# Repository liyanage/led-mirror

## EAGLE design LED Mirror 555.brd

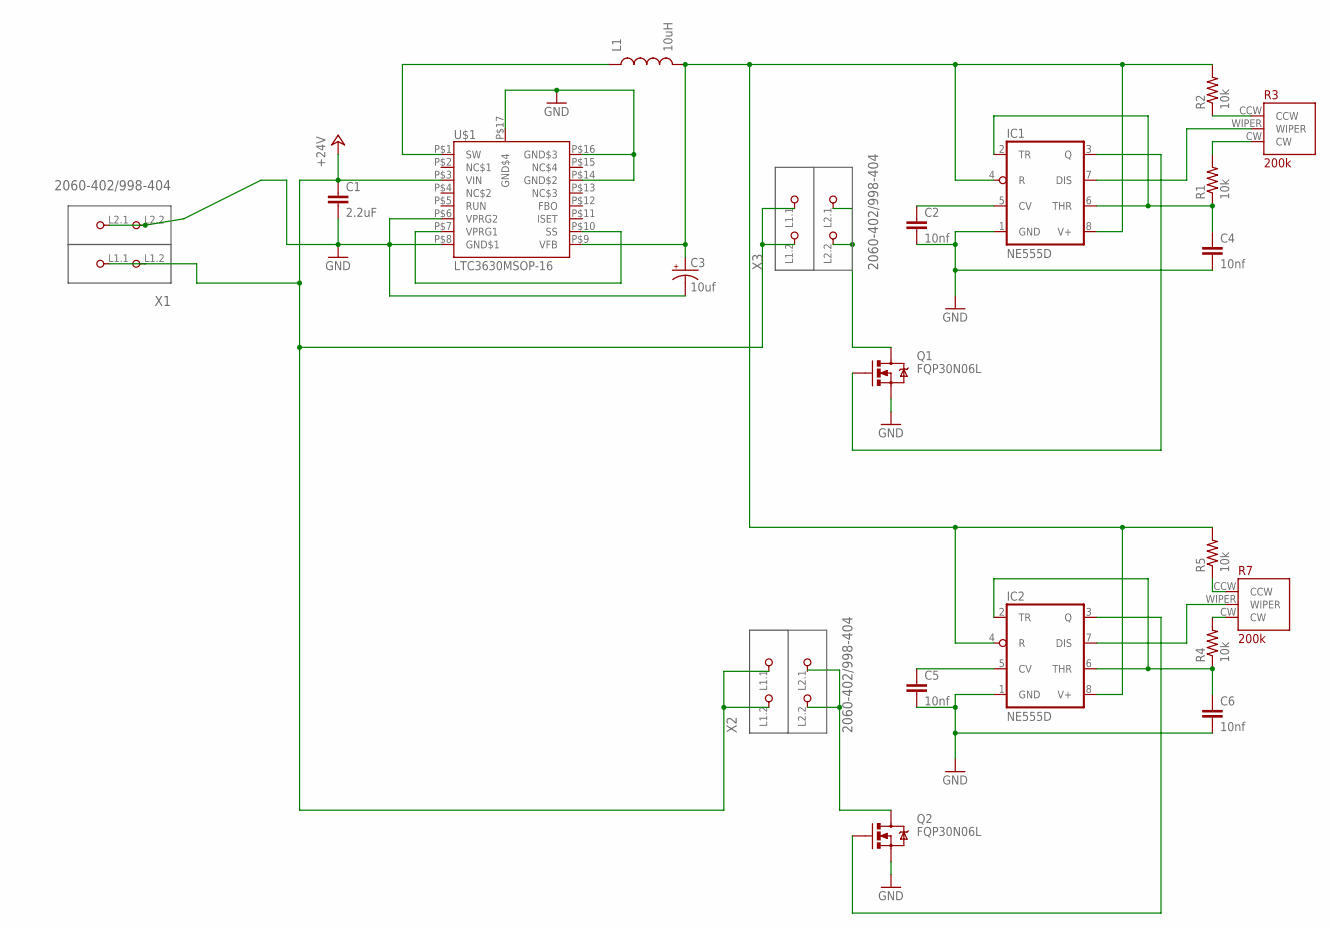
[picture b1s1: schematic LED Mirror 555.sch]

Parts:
C1: 2.2uF; 0805
C2, C4, C5, C6: 10nf; 0805
C3: 10uf; EIA3216
IC1, IC2: NE555D; SO08
L1: 10uH; NPI75C
Q1, Q2: FQP30N06L; TO220V
R1, R2, R4, R5: 10k; 0805
R3, R7: 200k; TRIMPOT_3296_SMD
U$1: LTC3630MSOP-16; MSOP-16
X1, X2, X3: 2060-402/998-404; P-2060-402/998-404

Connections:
+24V: C1.1, U$1.P$3 (VIN), X1.L1.1 (P1.1), X1.L1.2 (P1.2), X2.L1.1 (P1.1), X2.L1.2 (P1.2), X3.L1.1 (P1.1), X3.L1.2 (P1.2)
GND: C1.2, C2.2, C3.C (-), C4.2, C5.2, C6.2, IC1.1 (GND), IC2.1 (GND), Q1.3 (S), Q2.3 (S), U$1.P$6 (VPRG2), U$1.P$8 (GND$1), U$1.P$14 (GND$2), U$1.P$16 (GND$3), U$1.P$17 (GND$4), X1.L2.1 (P2.1), X1.L2.2 (P2.2)
unnamed: U$1.P$7 (VPRG1), U$1.P$10 (SS)
unnamed: L1.1, U$1.P$1 (SW)
unnamed: C3.A (+), IC1.4 (R), IC1.8 (V+), IC2.4 (R), IC2.8 (V+), L1.2, R2.2, R5.2, U$1.P$9 (VFB)
unnamed: IC1.3 (Q), Q1.1 (G)
unnamed: Q1.2 (D), X3.L2.1 (P2.1), X3.L2.2 (P2.2)
unnamed: R2.1, R3.CCW
unnamed: R1.2, R3.CW
unnamed: C2.1, IC1.5 (CV)
unnamed: IC1.7 (DIS), R3.WIPER
unnamed: C4.1, IC1.2 (TR), IC1.6 (THR), R1.1
unnamed: R4.2, R7.CW
unnamed: Q2.2 (D), X2.L2.2 (P2.2)
unnamed: IC2.3 (Q), Q2.1 (G)
unnamed: C5.1, IC2.5 (CV)
unnamed: C6.1, IC2.2 (TR), IC2.6 (THR), R4.1
unnamed: R5.1, R7.CCW
unnamed: IC2.7 (DIS), R7.WIPER

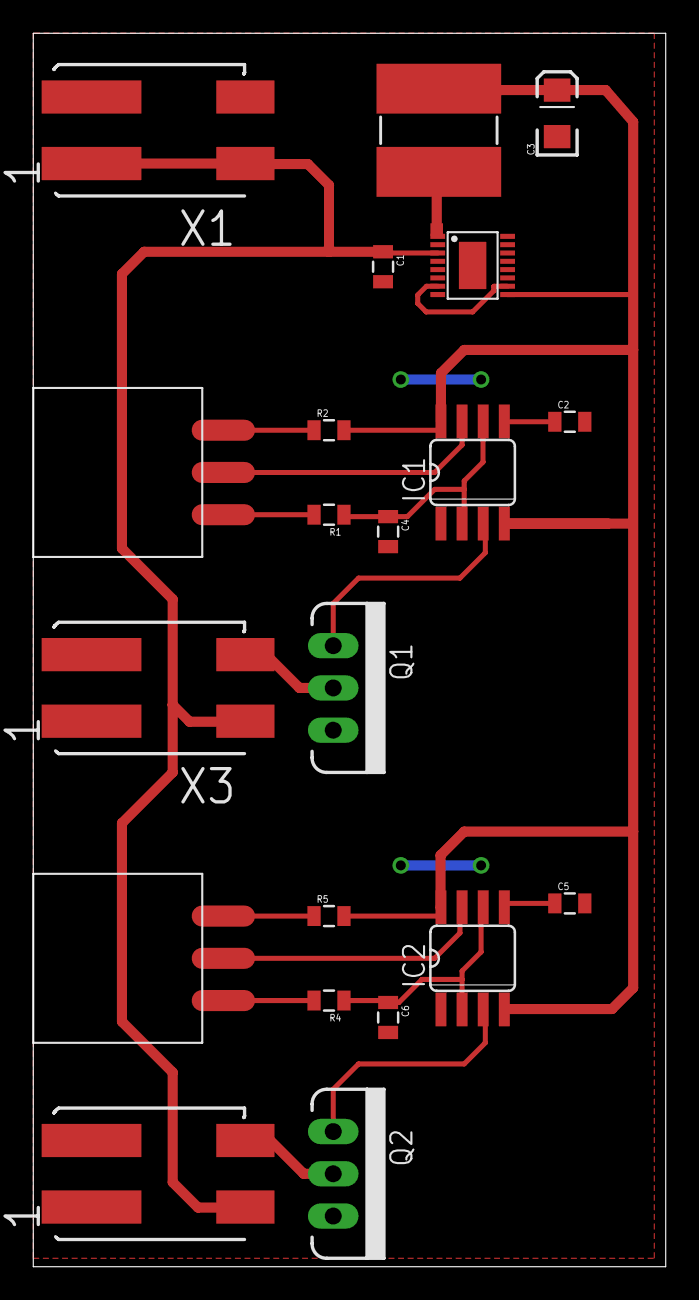
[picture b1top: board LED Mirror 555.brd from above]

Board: 2 copper layers, 38.0 x 74.2 mm, 21 parts (0 on the bottom side), 19 nets.

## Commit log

2015-10-20 init

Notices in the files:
parts and their libraries:
SparkFun-Capacitors: Licensing: Creative Commons ShareAlike 4.0 International - https://creativecommons.org/licenses/by-sa/4.0
